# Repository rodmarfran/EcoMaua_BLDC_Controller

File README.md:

# EcoMaua_Dev
Repositório para desenvolvimentos do EcoMaua

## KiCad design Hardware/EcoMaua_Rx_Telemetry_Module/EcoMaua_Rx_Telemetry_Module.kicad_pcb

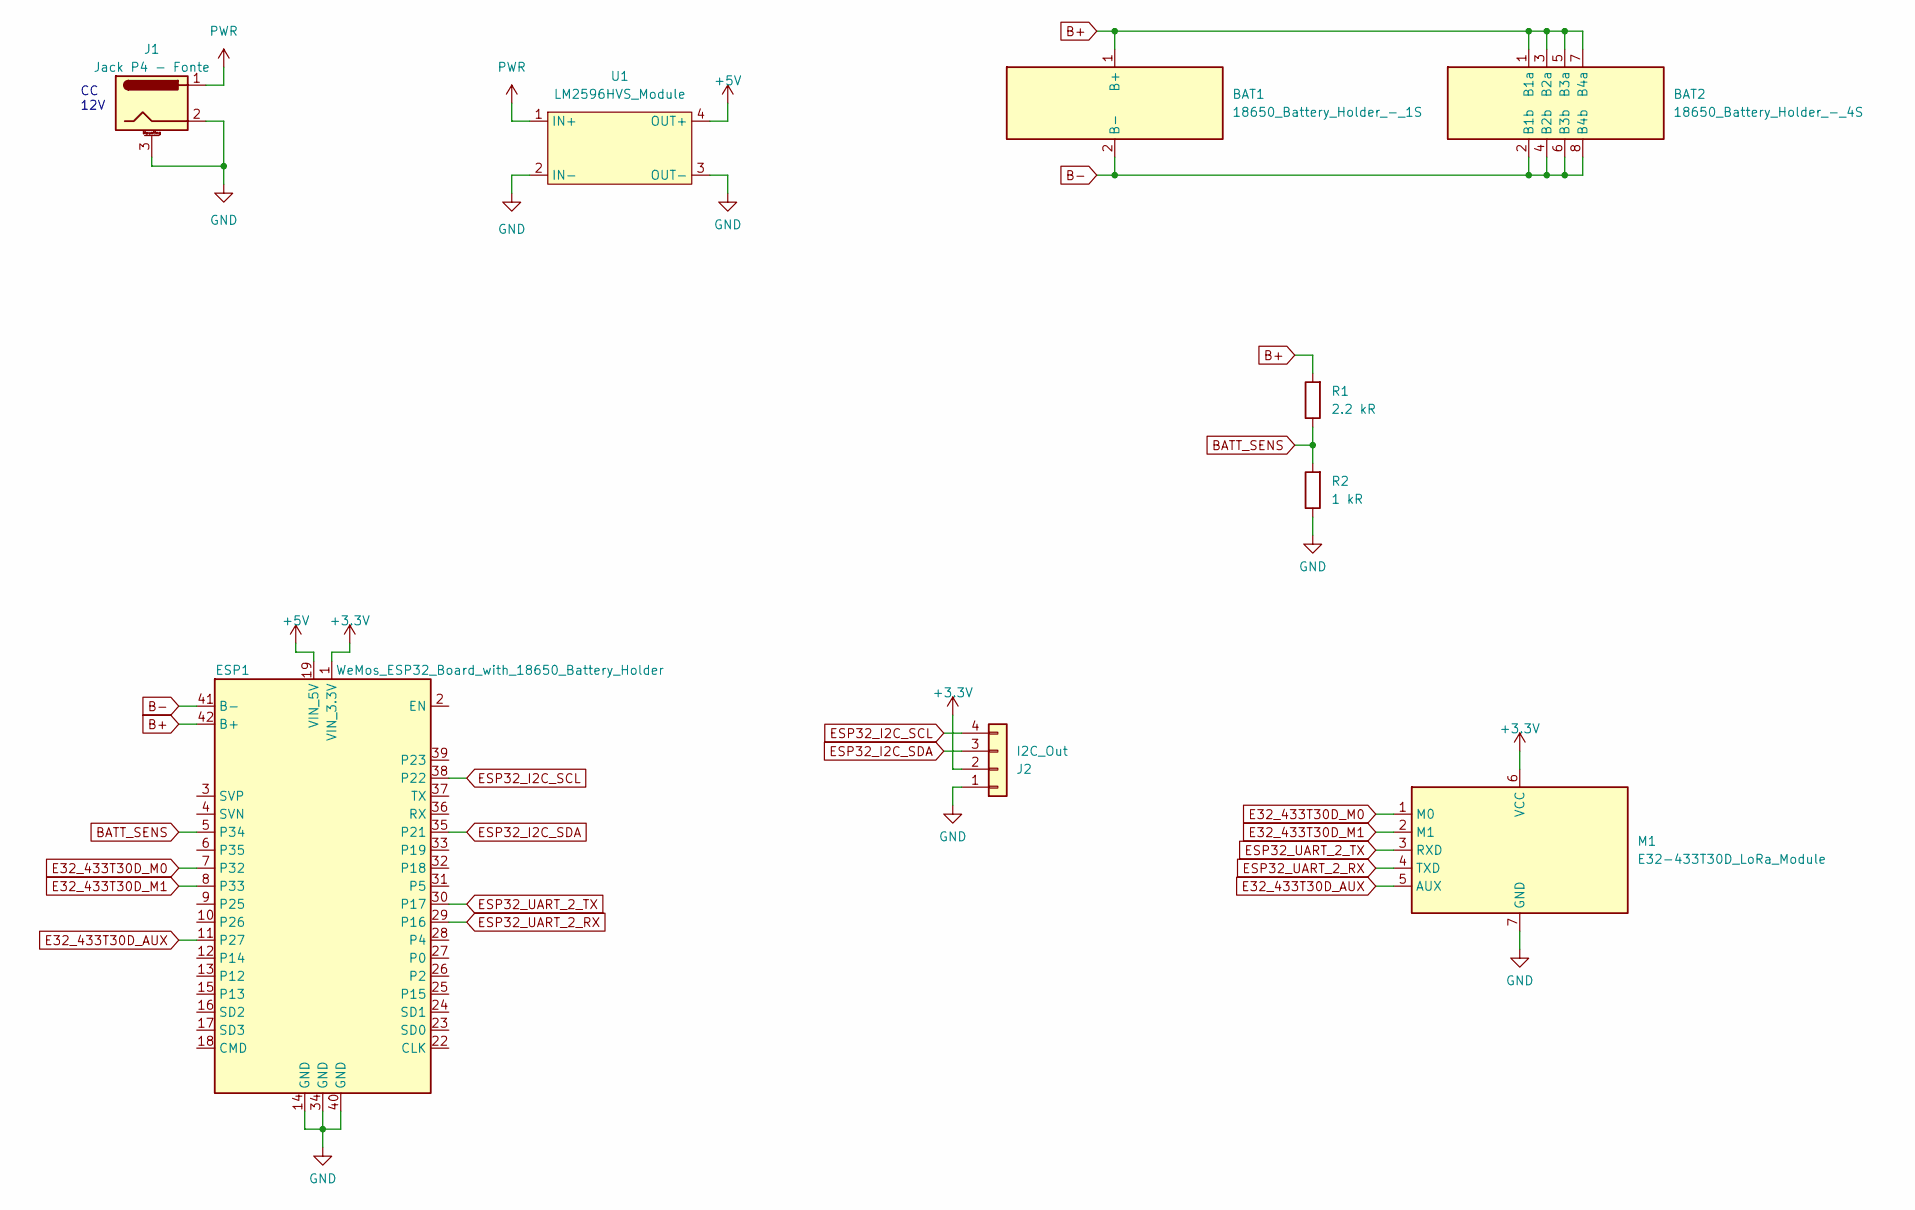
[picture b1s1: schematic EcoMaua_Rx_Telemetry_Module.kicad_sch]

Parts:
BAT1: 18650_Battery_Holder_-_1S; 18650 Battery Holder - 1S
BAT2: 18650_Battery_Holder_-_4S; 18650 Battery Holder - 4S
ESP1: WeMos_ESP32_Board_with_18650_Battery_Holder; WeMos ESP32 Board with 18650 Battery Holder
J1: Jack P4 - Fonte; BarrelJack_Horizontal
J2: I2C_Out; PinHeader_1x04_P2.54mm_Vertical
M1: E32-433T30D_LoRa_Module; E32-433T30D LoRa Module
R1: 2.2 kR; R_Axial_DIN0207_L6.3mm_D2.5mm_P10.16mm_Horizontal
R2: 1 kR; R_Axial_DIN0207_L6.3mm_D2.5mm_P10.16mm_Horizontal
U1: LM2596HVS_Module; LM2596HVS_Module_PDIP

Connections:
+3.3V: ESP1.1 (VIN_3.3V), J2.2, M1.6 (VCC)
+5V: ESP1.19 (VIN_5V), U1.4 (OUT+)
B+: BAT1.1 (B+), BAT2.1 (B1a), BAT2.3 (B2a), BAT2.5 (B3a), BAT2.7 (B4a), ESP1.42 (B+), R1.2
B-: BAT1.2 (B-), BAT2.2 (B1b), BAT2.4 (B2b), BAT2.6 (B3b), BAT2.8 (B4b), ESP1.41 (B-)
BATT_SENS: ESP1.5 (P34), R1.1, R2.2
E32_433T30D_AUX: ESP1.11 (P27), M1.5 (AUX)
E32_433T30D_M0: ESP1.7 (P32), M1.1 (M0)
E32_433T30D_M1: ESP1.8 (P33), M1.2 (M1)
ESP32_I2C_SCL: ESP1.38 (P22), J2.4
ESP32_I2C_SDA: ESP1.35 (P21), J2.3
ESP32_UART_2_RX: ESP1.29 (P16), M1.4 (TXD)
ESP32_UART_2_TX: ESP1.30 (P17), M1.3 (RXD)
GND: ESP1.14 (GND), ESP1.34 (GND), ESP1.40 (GND), J1.2, J1.3 (MountPin), J2.1, M1.7 (GND), R2.1, U1.2 (IN-), U1.3 (OUT-)
PWR: J1.1, U1.1 (IN+)

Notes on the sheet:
CC 12V

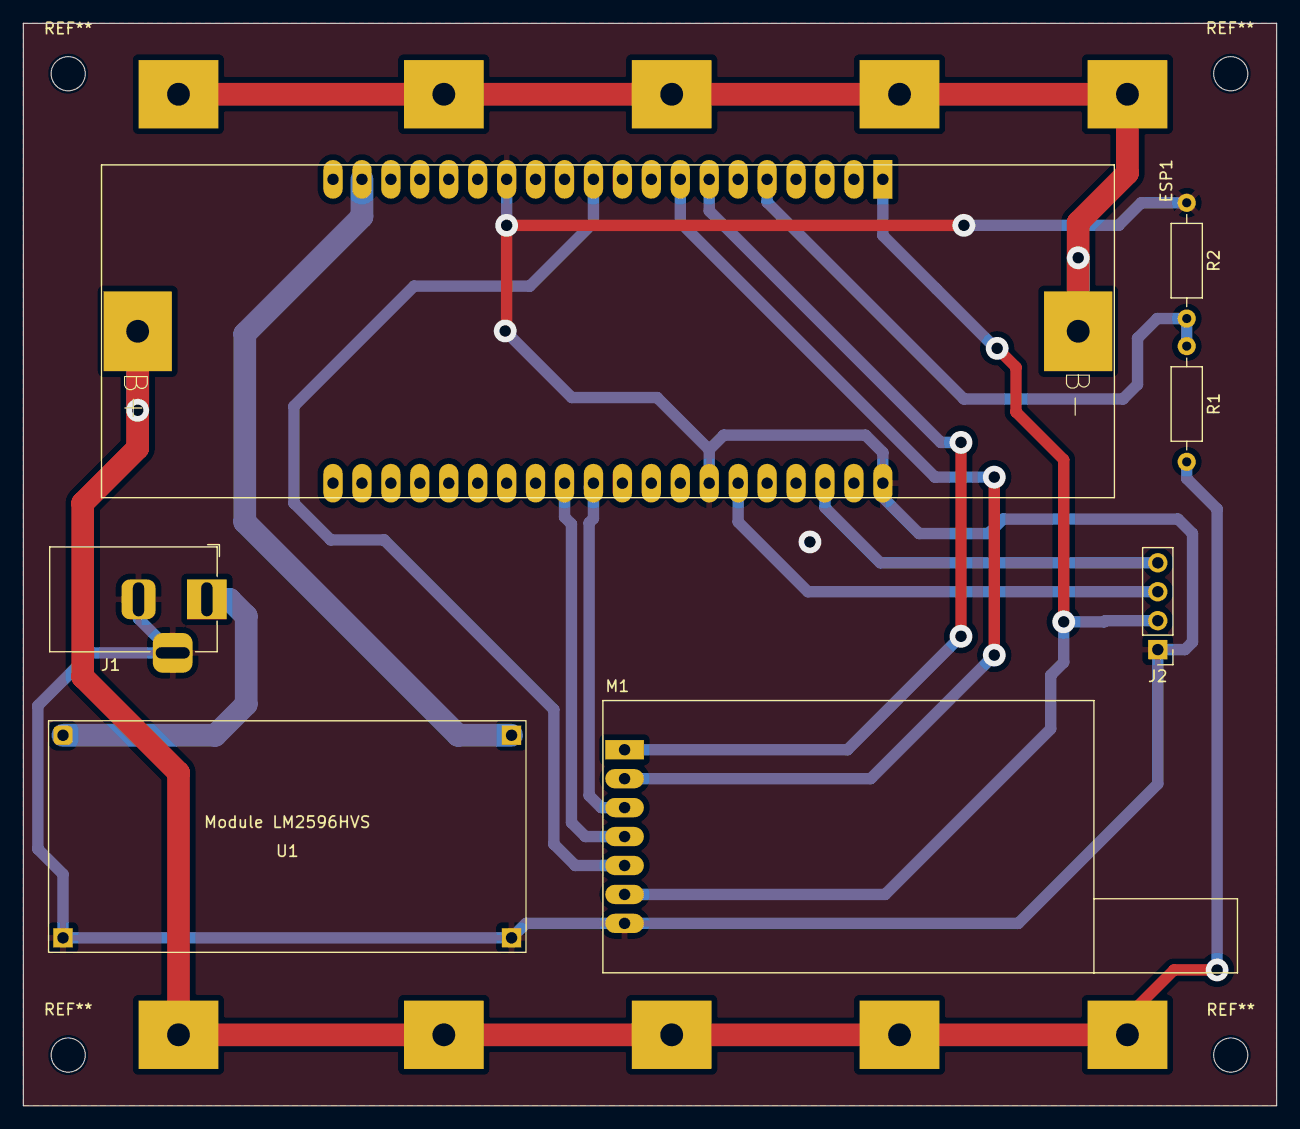
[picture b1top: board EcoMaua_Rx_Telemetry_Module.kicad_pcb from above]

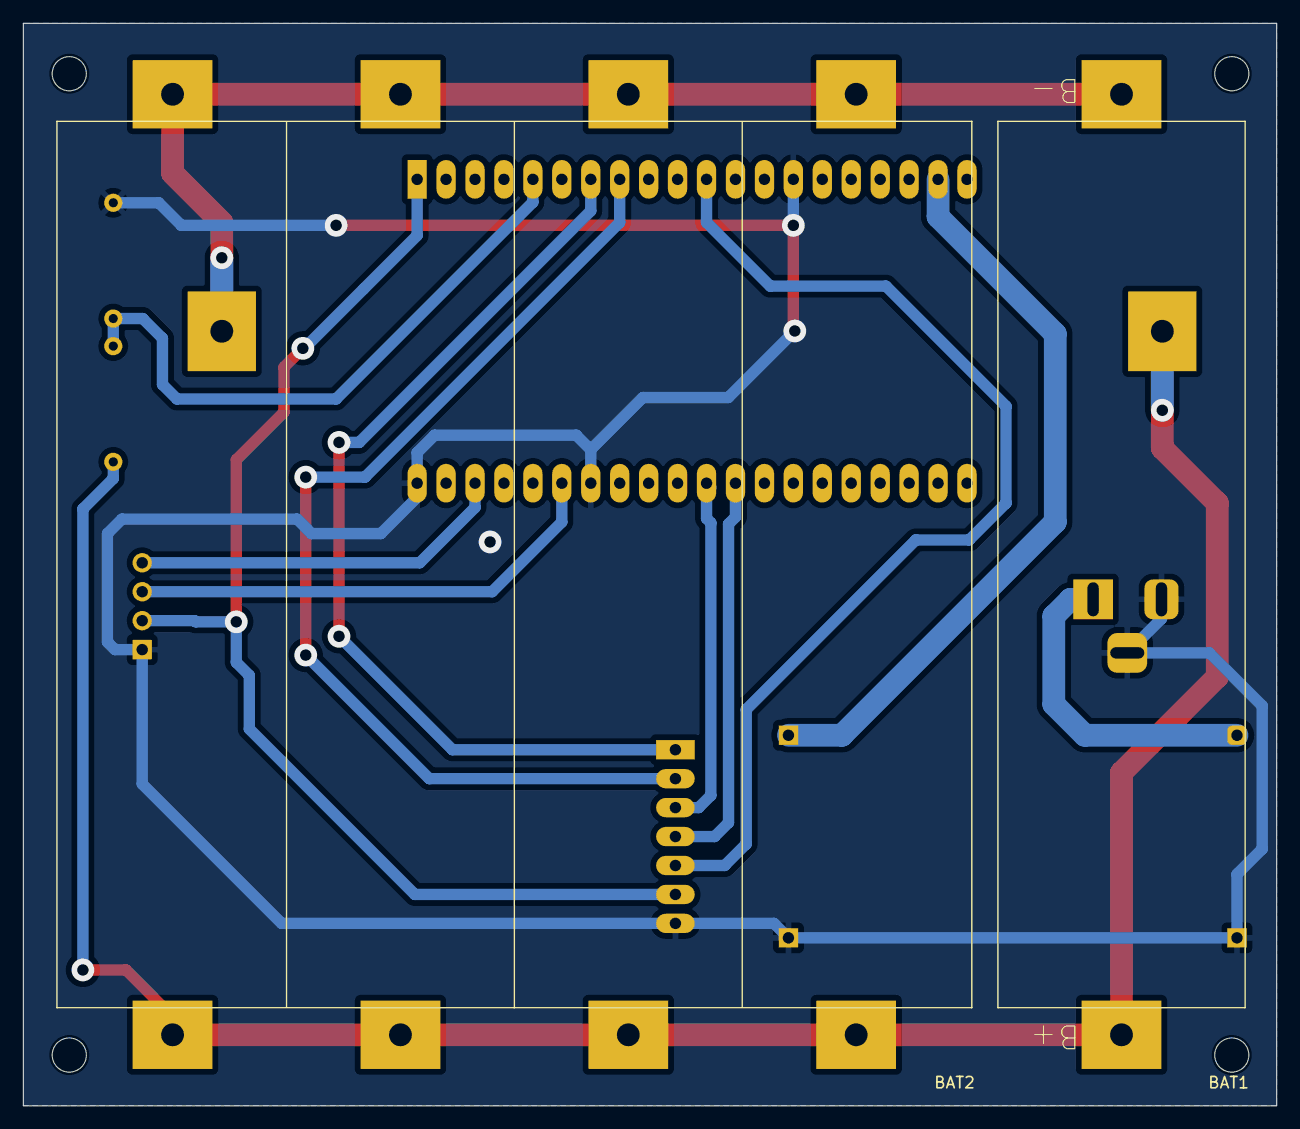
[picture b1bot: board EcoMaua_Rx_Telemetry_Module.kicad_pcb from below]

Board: 2 copper layers, 110.0 x 95.0 mm, 9 parts (2 on the bottom side), 14 nets.

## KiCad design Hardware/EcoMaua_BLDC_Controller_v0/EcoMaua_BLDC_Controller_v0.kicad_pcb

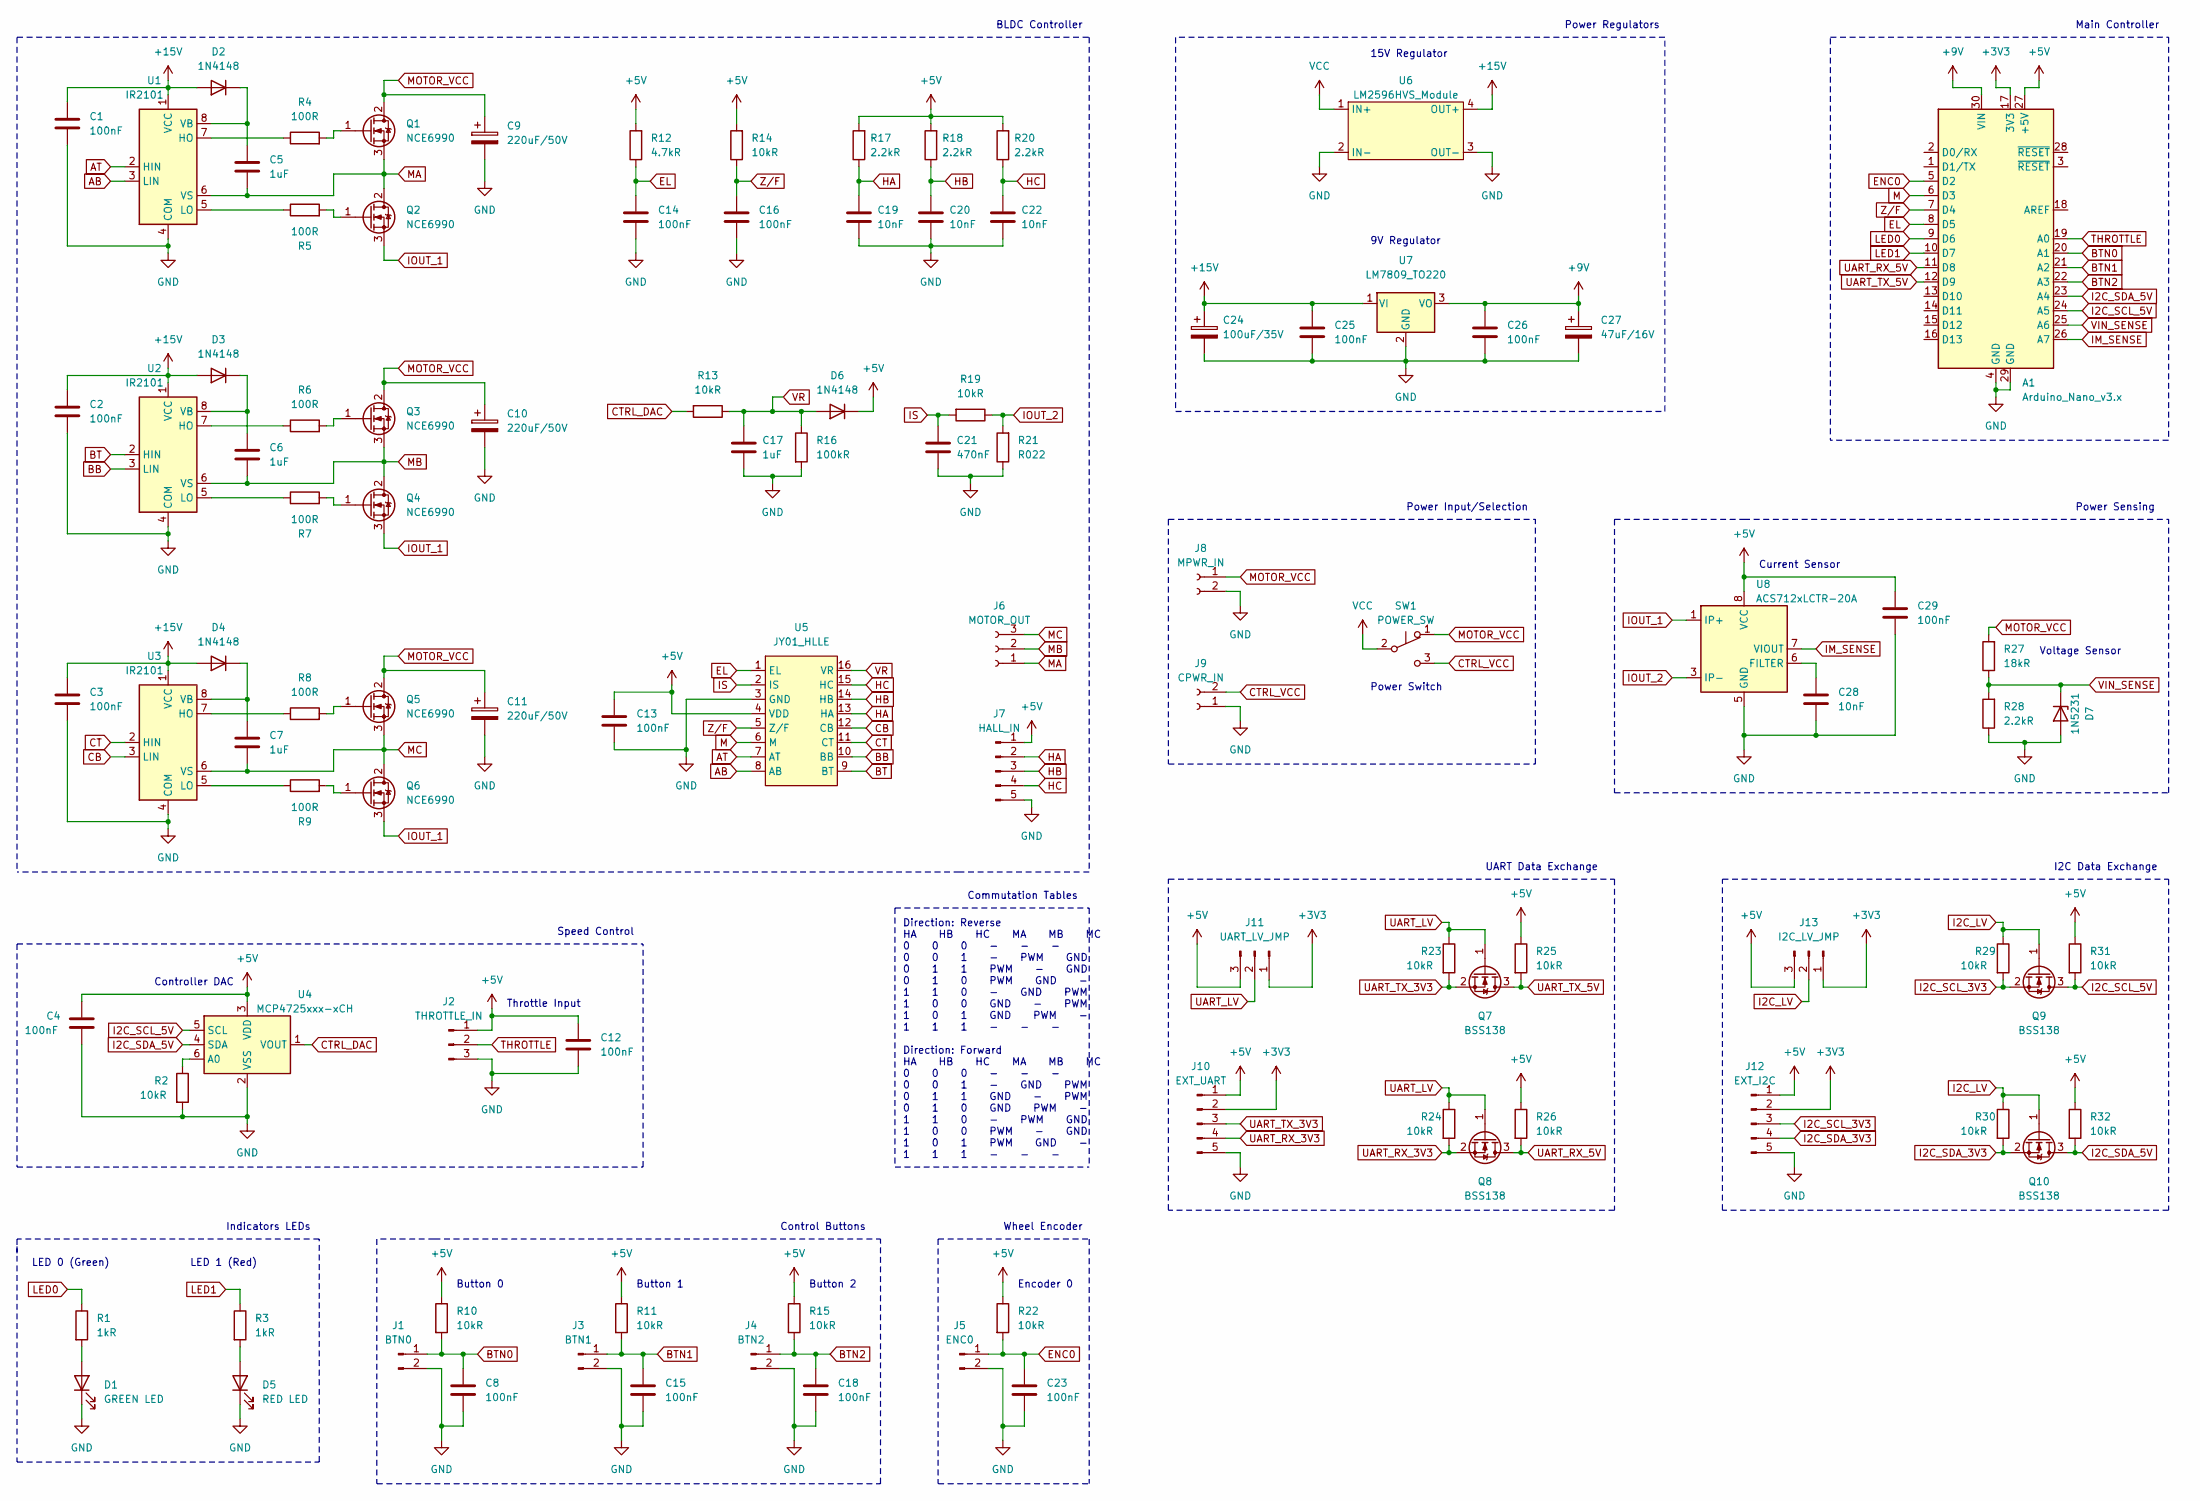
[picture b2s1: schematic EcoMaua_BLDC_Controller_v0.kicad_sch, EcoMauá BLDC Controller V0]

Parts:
A1: Arduino_Nano_v3.x; Arduino_Nano
C1, C2, C3, C4, C8, C12, C13, C14, C15, C16, C18, C23, C25, C26, C29: 100nF; C_0805_2012Metric
C5, C6, C7, C17: 1uF; C_0805_2012Metric
C9, C10, C11: 220uF/50V; CP_Elec_10x10.5
C19, C20, C22, C28: 10nF; C_0805_2012Metric
C21: 470nF; C_0805_2012Metric
C24: 100uF/35V; CP_Elec_6.3x7.7
C27: 47uF/16V; CP_Elec_5x5.4
D1: GREEN LED; LED_0805_2012Metric
D2, D3, D4, D6: 1N4148; D_MiniMELF
D5: RED LED; LED_0805_2012Metric
D7: 1N5231; D_MiniMELF
J1: BTN0; PinHeader_1x02_P2.54mm_Vertical
J2: THROTTLE_IN; PinHeader_1x03_P2.54mm_Vertical
J3: BTN1; PinHeader_1x02_P2.54mm_Vertical
J4: BTN2; PinHeader_1x02_P2.54mm_Vertical
J5: ENC0; PinHeader_1x02_P2.54mm_Vertical
J6: MOTOR_OUT; PhoenixContact_MSTBVA_2,5_3-G-5,08_1x03_P5.08mm_Vertical
J7: HALL_IN; PinHeader_1x05_P2.54mm_Vertical
J8: MPWR_IN; PhoenixContact_MSTBVA_2,5_2-G-5,08_1x02_P5.08mm_Vertical
J9: CPWR_IN; PinHeader_1x02_P2.54mm_Vertical
J10: EXT_UART; PinHeader_1x05_P2.54mm_Vertical
J11: UART_LV_JMP; PinHeader_1x03_P2.54mm_Vertical
J12: EXT_I2C; PinHeader_1x05_P2.54mm_Vertical
J13: I2C_LV_JMP; PinHeader_1x03_P2.54mm_Vertical
Q1, Q2, Q3, Q4, Q5, Q6: NCE6990; TO-220-3_Horizontal_TabUp_NoHole_F
Q7, Q8, Q9, Q10: BSS138; SOT-23
R1, R3: 1kR; R_0805_2012Metric
R2, R10, R11, R13, R14, R15, R19, R22, R23, R24, R25, R26, R29, R30, R31, R32: 10kR; R_0805_2012Metric
R4, R5, R6, R7, R8, R9: 100R; R_1206_3216Metric
R12: 4.7kR; R_0805_2012Metric
R16: 100kR; R_0805_2012Metric
R17, R18, R20, R28: 2.2kR; R_0805_2012Metric
R21: R022; R_Bare_Metal_Element_L11.4mm_W3.8mm_P10.2mm
R27: 18kR; R_0805_2012Metric
SW1: POWER_SW; SS_Slide_1P2T_SS12F64
U1, U2, U3: IR2101; SOIC-8_3.9x4.9mm_P1.27mm
U4: MCP4725xxx-xCH; SOT-23-6
U5: JY01_HLLE; SOP-16_3.9x9.9mm_P1.27mm
U6: LM2596HVS_Module; LM2596HVS_Module_PDIP
U7: LM7809_TO220; TO-220-3_Horizontal_TabDown
U8: ACS712xLCTR-20A; SOIC-8_3.9x4.9mm_P1.27mm

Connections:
+3V3: A1.17 (3V3), J10.2, J11.1, J12.2, J13.1
+5V: A1.27 (+5V), C4.1, C12.1, C13.1, C29.1, D6.1 (K), J2.1, J7.1, J10.1, J11.3, J12.1, J13.3, R10.1, R11.1, R12.2, R14.2, R15.1, R17.2, R18.2, R20.2, R22.1, R25.1, R26.1, R31.1, R32.1, U4.3 (VDD), U5.4 (VDD), U8.8 (VCC)
+9V: A1.30 (VIN), C26.1, C27.1, U7.3 (VO)
+15V: C1.1, C2.1, C3.1, C24.1, C25.1, D2.2 (A), D3.2 (A), D4.2 (A), U1.1 (VCC), U2.1 (VCC), U3.1 (VCC), U6.4 (OUT+), U7.1 (VI)
AB: U1.3 (LIN), U5.8 (AB)
AT: U1.2 (HIN), U5.7 (AT)
BB: U2.3 (LIN), U5.10 (BB)
BT: U2.2 (HIN), U5.9 (BT)
BTN0: A1.20 (A1), C8.1, J1.1, R10.2
BTN1: A1.21 (A2), C15.1, J3.1, R11.2
BTN2: A1.22 (A3), C18.1, J4.1, R15.2
CB: U3.3 (LIN), U5.12 (CB)
CT: U3.2 (HIN), U5.11 (CT)
CTRL_DAC: R13.2, U4.1 (VOUT)
CTRL_VCC: J9.2, SW1.3 (C)
EL: A1.8 (D5), C14.1, R12.1, U5.1 (EL)
ENC0: A1.5 (D2), C23.1, J5.1, R22.2
GND: A1.4 (GND), A1.29 (GND), C1.2, C2.2, C3.2, C4.2, C8.2, C9.2, C10.2, C11.2, C12.2, C13.2, C14.2, C15.2, C16.2, C17.2, C18.2, C19.2, C20.2, C21.2, C22.2, C23.2, C24.2, C25.2, C26.2, C27.2, C28.2, C29.2, D1.1 (K), D5.1 (K), D7.2 (A), J1.2, J2.3, J3.2, J4.2, J5.2, J7.5, J8.2, J9.1, J10.5, J12.5, R2.2, R16.2, R21.1, R28.1, U1.4 (COM), U2.4 (COM), U3.4 (COM), U4.2 (VSS), U5.3 (GND), U6.2 (IN-), U6.3 (OUT-), U7.2 (GND), U8.5 (GND)
HA: C19.1, J7.2, R17.1, U5.13 (HA)
HB: C20.1, J7.3, R18.1, U5.14 (HB)
HC: C22.1, J7.4, R20.1, U5.15 (HC)
I2C_LV: J13.2, Q9.1 (G), Q10.1 (G), R29.1, R30.1
I2C_SCL_3V3: J12.3, Q9.2 (S), R29.2
I2C_SCL_5V: A1.24 (A5), Q9.3 (D), R31.2, U4.5 (SCL)
I2C_SDA_3V3: J12.4, Q10.2 (S), R30.2
I2C_SDA_5V: A1.23 (A4), Q10.3 (D), R32.2, U4.4 (SDA)
IM_SENSE: A1.26 (A7), U8.7 (VIOUT)
IOUT_1: Q2.3 (S), Q4.3 (S), Q6.3 (S), U8.1 (IP+), U8.2 (IP+)
IOUT_2: R19.1, R21.2, U8.3 (IP-), U8.4 (IP-)
IS: C21.1, R19.2, U5.2 (IS)
LED0: A1.9 (D6), R1.1
LED1: A1.10 (D7), R3.1
M: A1.6 (D3), U5.6 (M)
MA: C5.2, J6.1, Q1.3 (S), Q2.2 (D), U1.6 (VS)
MB: C6.2, J6.2, Q3.3 (S), Q4.2 (D), U2.6 (VS)
MC: C7.2, J6.3, Q5.3 (S), Q6.2 (D), U3.6 (VS)
MOTOR_VCC: C9.1, C10.1, C11.1, J8.1, Q1.2 (D), Q3.2 (D), Q5.2 (D), R27.2, SW1.1 (A)
unnamed: C5.1, D2.1 (K), U1.8 (VB)
unnamed: C6.1, D3.1 (K), U2.8 (VB)
unnamed: C7.1, D4.1 (K), U3.8 (VB)
unnamed: C28.1, U8.6 (FILTER)
unnamed: D1.2 (A), R1.2
unnamed: D5.2 (A), R3.2
unnamed: Q1.1 (G), R4.2
unnamed: Q2.1 (G), R5.2
unnamed: Q3.1 (G), R6.2
unnamed: Q4.1 (G), R7.2
unnamed: Q5.1 (G), R8.2
unnamed: Q6.1 (G), R9.2
unnamed: R2.1, U4.6 (A0)
unnamed: R4.1, U1.7 (HO)
unnamed: R5.1, U1.5 (LO)
unnamed: R6.1, U2.7 (HO)
unnamed: R7.1, U2.5 (LO)
unnamed: R8.1, U3.7 (HO)
unnamed: R9.1, U3.5 (LO)
THROTTLE: A1.19 (A0), J2.2
UART_LV: J11.2, Q7.1 (G), Q8.1 (G), R23.1, R24.1
UART_RX_3V3: J10.4, Q8.2 (S), R24.2
UART_RX_5V: A1.11 (D8), Q8.3 (D), R26.2
UART_TX_3V3: J10.3, Q7.2 (S), R23.2
UART_TX_5V: A1.12 (D9), Q7.3 (D), R25.2
VCC: SW1.2 (B), U6.1 (IN+)
VIN_SENSE: A1.25 (A6), D7.1 (K), R27.1, R28.2
VR: C17.1, D6.2 (A), R13.1, R16.1, U5.16 (VR)
Z/F: A1.7 (D4), C16.1, R14.1, U5.5 (Z/F)

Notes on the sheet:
I2C Data Exchange
BLDC Controller
Button 0
Direction: Reverse HA HB HC MA MB MC 0 0 0 - - - 0 0 1 - PWM GND 0 1 1 PWM - GND 0 1 0 PWM GND - 1 1 0 - GND PWM 1 0 0 GND - PWM 1 0 1 GND PWM - 1 1 1 - - - Direction: Forward HA HB HC MA MB MC 0 0 0 - - - 0 0 1 - GND PWM 0 1 1 GND - PWM 0 1 0 GND PWM - 1 1 0 - PWM GND 1 0 0 PWM - GND 1 0 1 PWM GND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
Throttle Input
Commutation Tables
Power Input/Selection
UART Data Exchange
9V Regulator
Wheel Encoder
Button 1
Power Regulators
LED 1 (Red)
Speed Control
Indicators LEDs
Controller DAC
Control Buttons
LED 0 (Green)
Main Controller
Voltage Sensor
Button 2
15V Regulator
Encoder 0
Power Sensing
Current Sensor
Power Switch

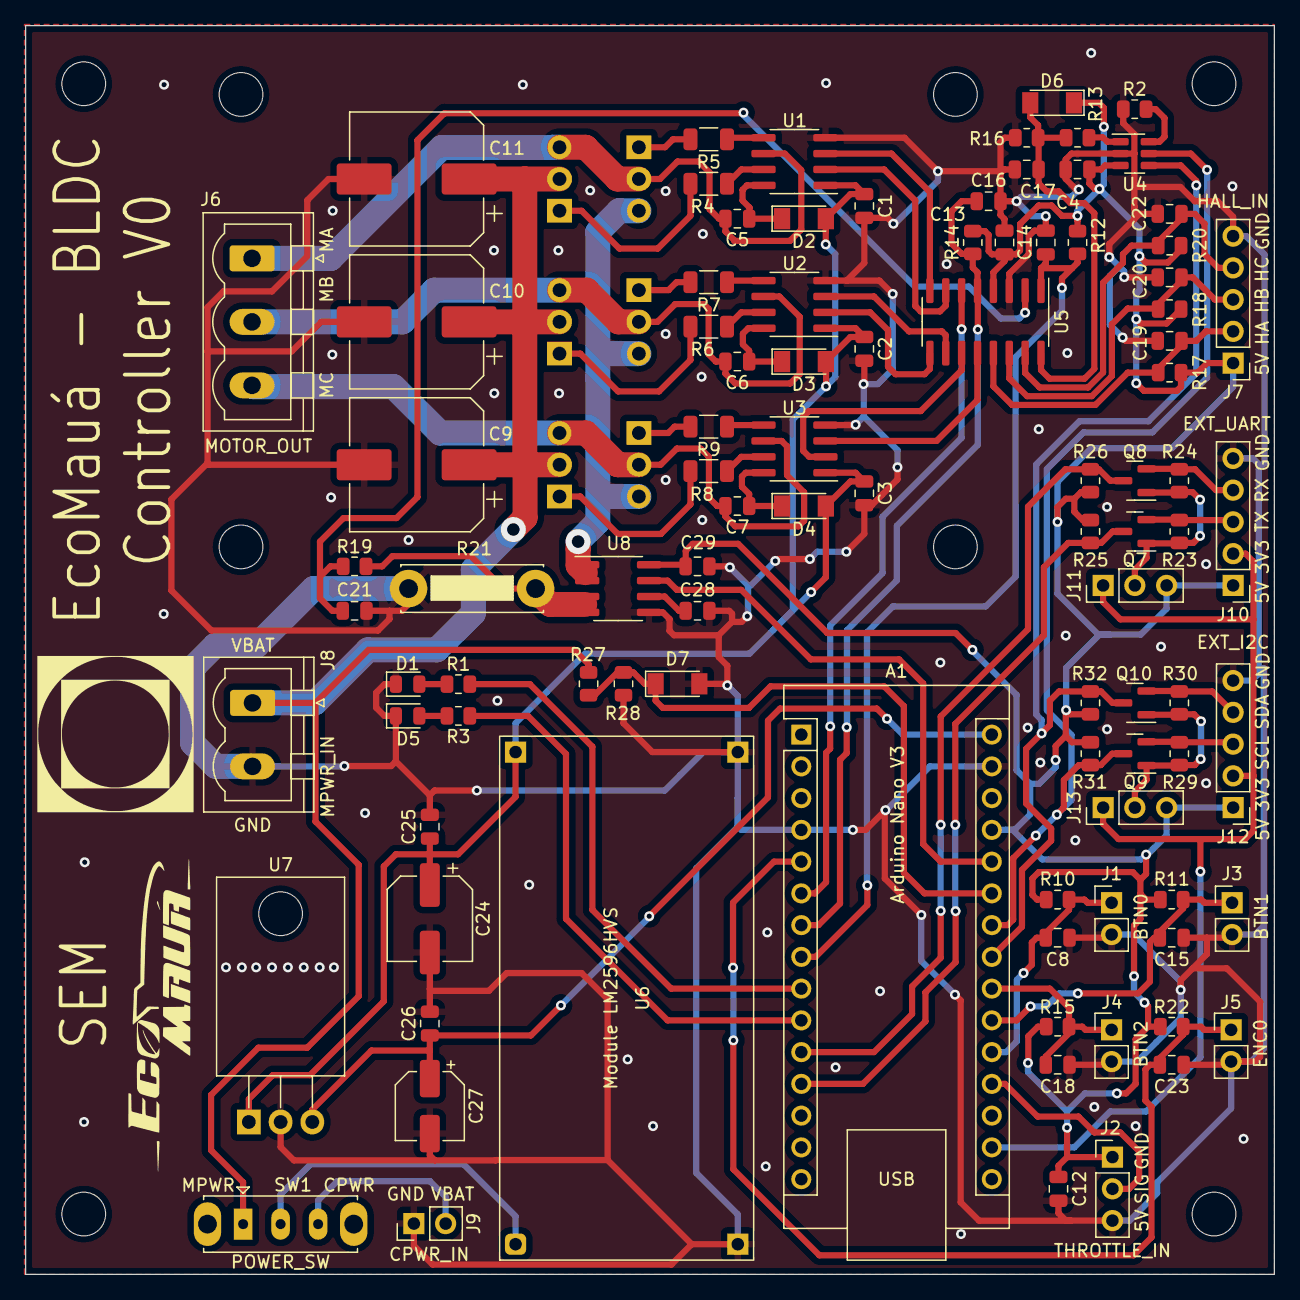
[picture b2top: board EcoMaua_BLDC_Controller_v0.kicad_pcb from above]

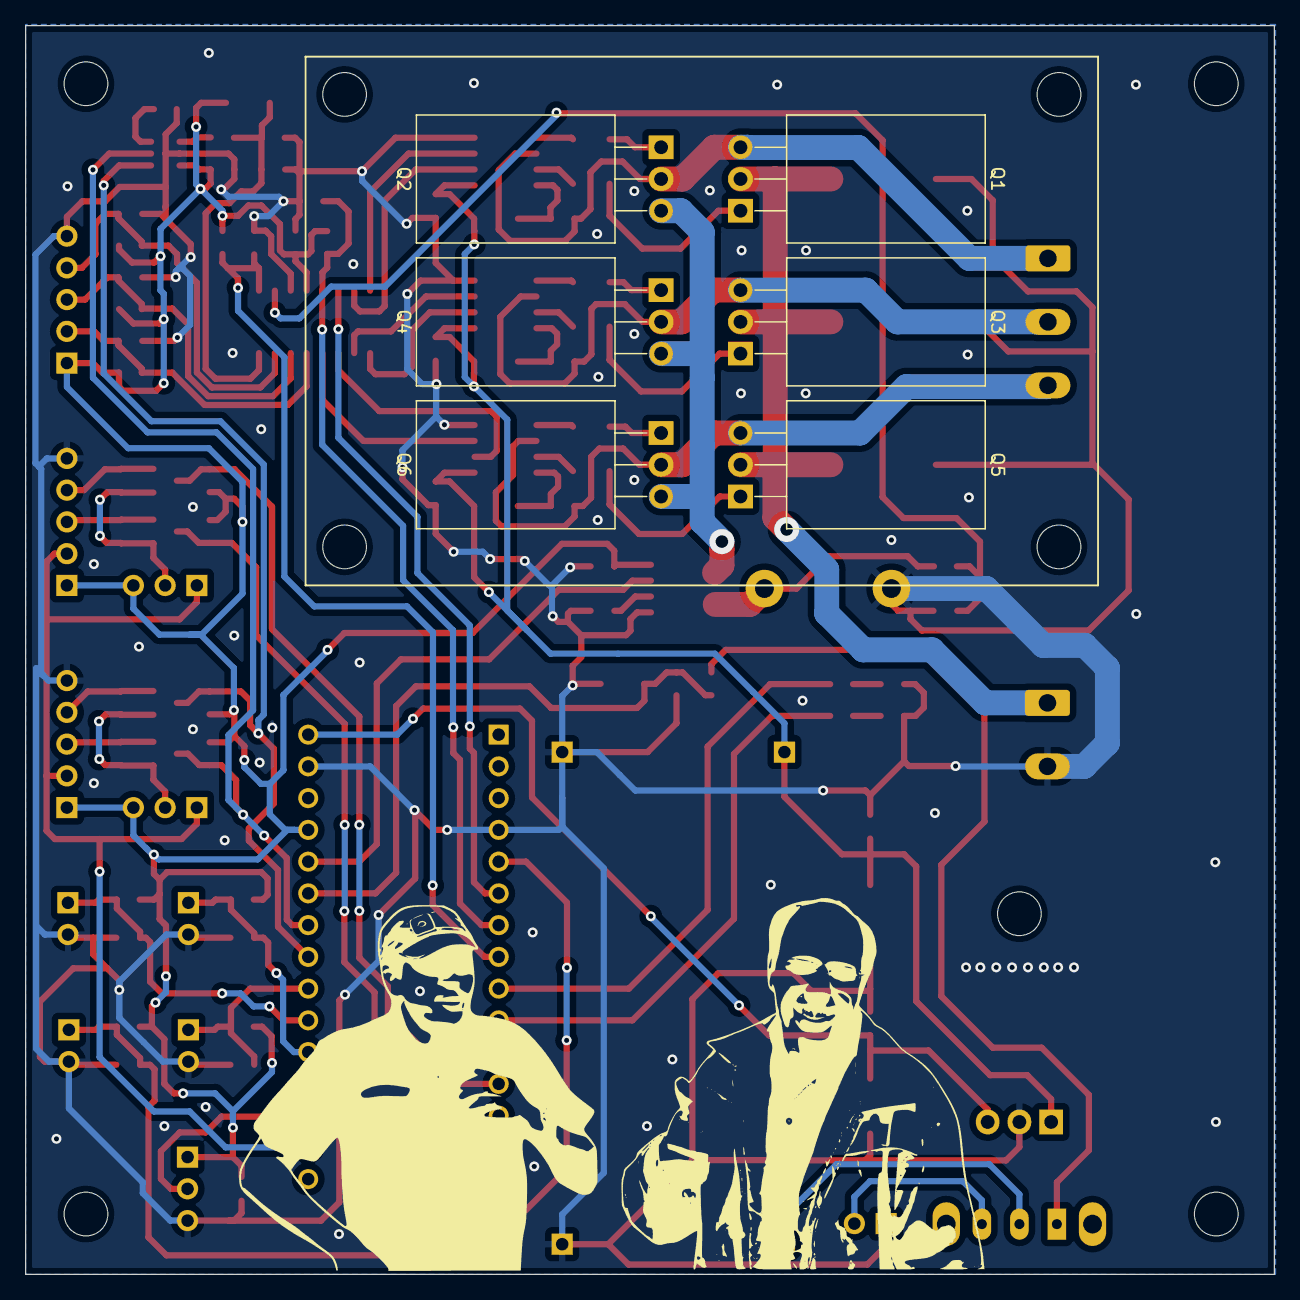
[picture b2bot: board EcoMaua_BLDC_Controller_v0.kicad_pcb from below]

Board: 2 copper layers, 99.9 x 99.9 mm, 109 parts (6 on the bottom side), 66 nets.

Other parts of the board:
MT1, MT2, MT3, MT4, MT5, MT6, MT7, MT8: MountingHole_3.5mm

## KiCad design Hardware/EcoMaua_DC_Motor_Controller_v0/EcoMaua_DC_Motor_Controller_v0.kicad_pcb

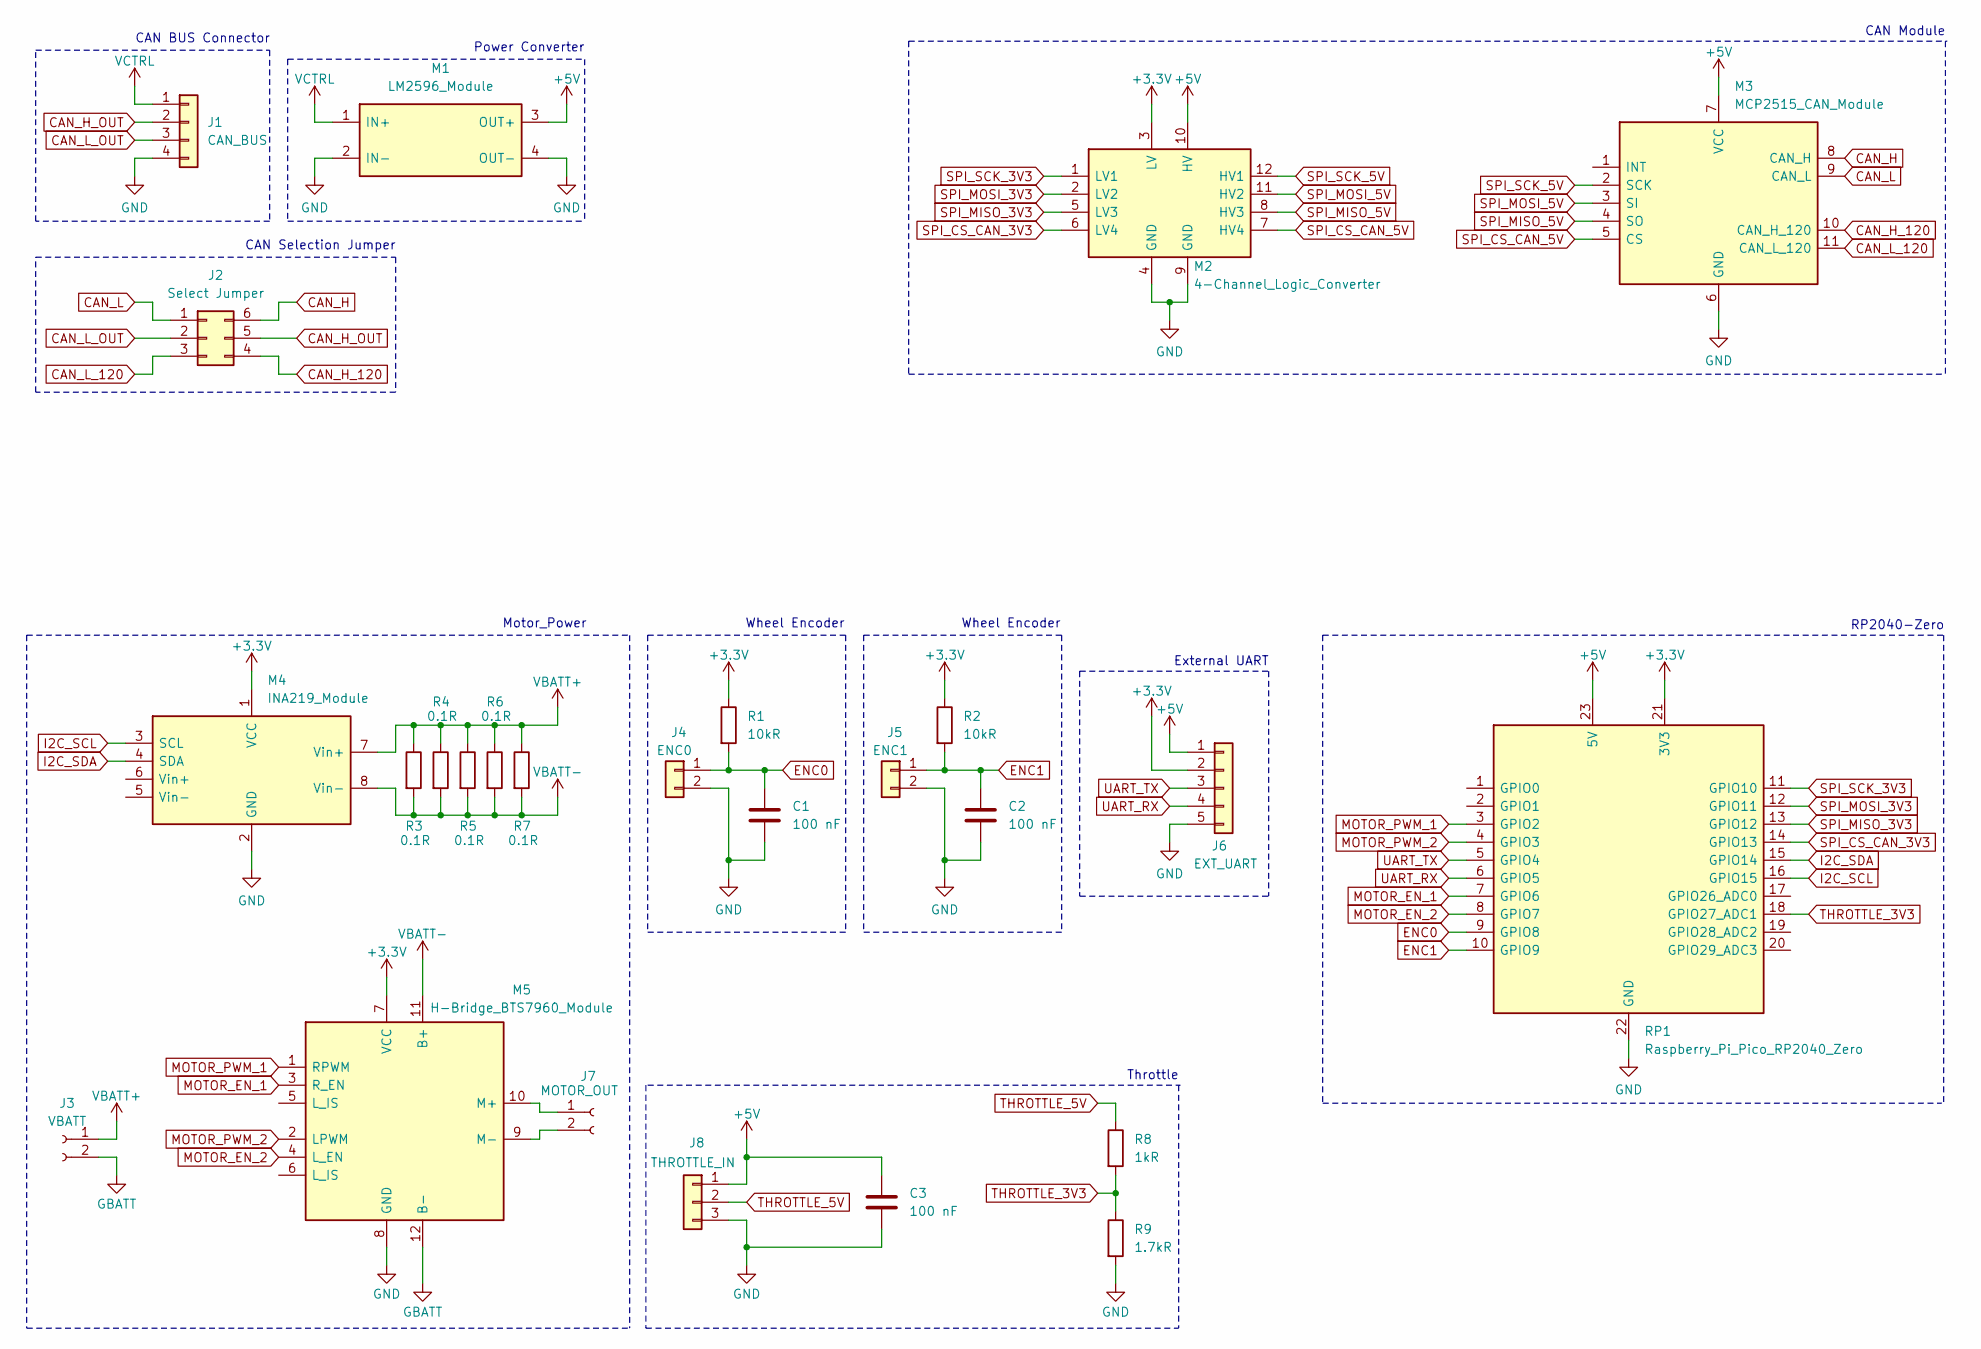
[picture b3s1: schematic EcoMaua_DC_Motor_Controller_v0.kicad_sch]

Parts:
C1, C2, C3: 100 nF; C_Disc_D3.0mm_W1.6mm_P2.50mm
J1: CAN_BUS; PinHeader_1x04_P2.54mm_Vertical_OP
J2: Select Jumper; PinHeader_2x03_P2.54mm_Vertical_OP
J3: VBATT; PhoenixContact_MSTBVA_2,5_2-G-5,08_1x02_P5.08mm_Vertical
J4: ENC0; PinHeader_1x02_P2.54mm_Vertical_OP
J5: ENC1; PinHeader_1x02_P2.54mm_Vertical_OP
J6: EXT_UART; PinHeader_1x05_P2.54mm_Vertical_OP
J7: MOTOR_OUT; PhoenixContact_MSTBVA_2,5_2-G-5,08_1x02_P5.08mm_Vertical
J8: THROTTLE_IN; PinHeader_1x03_P2.54mm_Vertical_OP
M1: LM2596_Module; LM2596 Module
M2: 4-Channel_Logic_Converter; 4-Channel Logic Converter
M3: MCP2515_CAN_Module; MCP2515_CAN Module
M4: INA219_Module; INA219 Module
M5: H-Bridge_BTS7960_Module; H-Bridge BTS7960 Module
R1, R2: 10kR; R_Axial_DIN0207_L6.3mm_D2.5mm_P15.24mm_Horizontal
R3, R4, R5, R6, R7: 0.1R; R_Axial_DIN0309_L9.0mm_D3.2mm_P25.40mm_Horizontal
R8: 1kR; R_Axial_DIN0207_L6.3mm_D2.5mm_P15.24mm_Horizontal
R9: 1.7kR; R_Axial_DIN0207_L6.3mm_D2.5mm_P15.24mm_Horizontal
RP1: Raspberry_Pi_Pico_RP2040_Zero; Raspberry Pi Pico RP2040 Zero

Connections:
+3.3V: J6.2, M2.3 (LV), M4.1 (VCC), M5.7 (VCC), R1.1, R2.1, RP1.21 (3V3)
+5V: C3.1, J6.1, J8.1, M1.3 (OUT+), M2.10 (HV), M3.7 (VCC), RP1.23 (5V)
CAN_H: J2.6, M3.8 (CAN_H)
CAN_H_120: J2.4, M3.10 (CAN_H_120)
CAN_H_OUT: J1.2, J2.5
CAN_L: J2.1, M3.9 (CAN_L)
CAN_L_120: J2.3, M3.11 (CAN_L_120)
CAN_L_OUT: J1.3, J2.2
ENC0: C1.1, J4.1, R1.2, RP1.9 (GPIO8)
ENC1: C2.1, J5.1, R2.2, RP1.10 (GPIO9)
GBATT: J3.2, M5.12 (B-)
GND: C1.2, C2.2, C3.2, J1.4, J4.2, J5.2, J6.5, J8.3, M1.2 (IN-), M1.4 (OUT-), M2.4 (GND), M2.9 (GND), M3.6 (GND), M4.2 (GND), M5.8 (GND), R9.2, RP1.22 (GND)
I2C_SCL: M4.3 (SCL), RP1.16 (GPIO15)
I2C_SDA: M4.4 (SDA), RP1.15 (GPIO14)
MOTOR_EN_1: M5.3 (R_EN), RP1.7 (GPIO6)
MOTOR_EN_2: M5.4 (L_EN), RP1.8 (GPIO7)
MOTOR_PWM_1: M5.1 (RPWM), RP1.3 (GPIO2)
MOTOR_PWM_2: M5.2 (LPWM), RP1.4 (GPIO3)
unnamed: J7.1, M5.10 (M+)
unnamed: J7.2, M5.9 (M-)
SPI_CS_CAN_3V3: M2.6 (LV4), RP1.14 (GPIO13)
SPI_CS_CAN_5V: M2.7 (HV4), M3.5 (CS)
SPI_MISO_3V3: M2.5 (LV3), RP1.13 (GPIO12)
SPI_MISO_5V: M2.8 (HV3), M3.4 (SO)
SPI_MOSI_3V3: M2.2 (LV2), RP1.12 (GPIO11)
SPI_MOSI_5V: M2.11 (HV2), M3.3 (SI)
SPI_SCK_3V3: M2.1 (LV1), RP1.11 (GPIO10)
SPI_SCK_5V: M2.12 (HV1), M3.2 (SCK)
THROTTLE_3V3: R8.2, R9.1, RP1.18 (GPIO27_ADC1)
THROTTLE_5V: J8.2, R8.1
UART_RX: J6.4, RP1.6 (GPIO5)
UART_TX: J6.3, RP1.5 (GPIO4)
VBATT+: J3.1, M4.7 (Vin+), R3.1, R4.1, R5.1, R6.1, R7.1
VBATT-: M4.8 (Vin-), M5.11 (B+), R3.2, R4.2, R5.2, R6.2, R7.2
VCTRL: J1.1, M1.1 (IN+)

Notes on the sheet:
CAN BUS Connector
Wheel Encoder
Throttle
CAN Module
CAN Selection Jumper
External UART
Motor_Power
RP2040-Zero
Power Converter

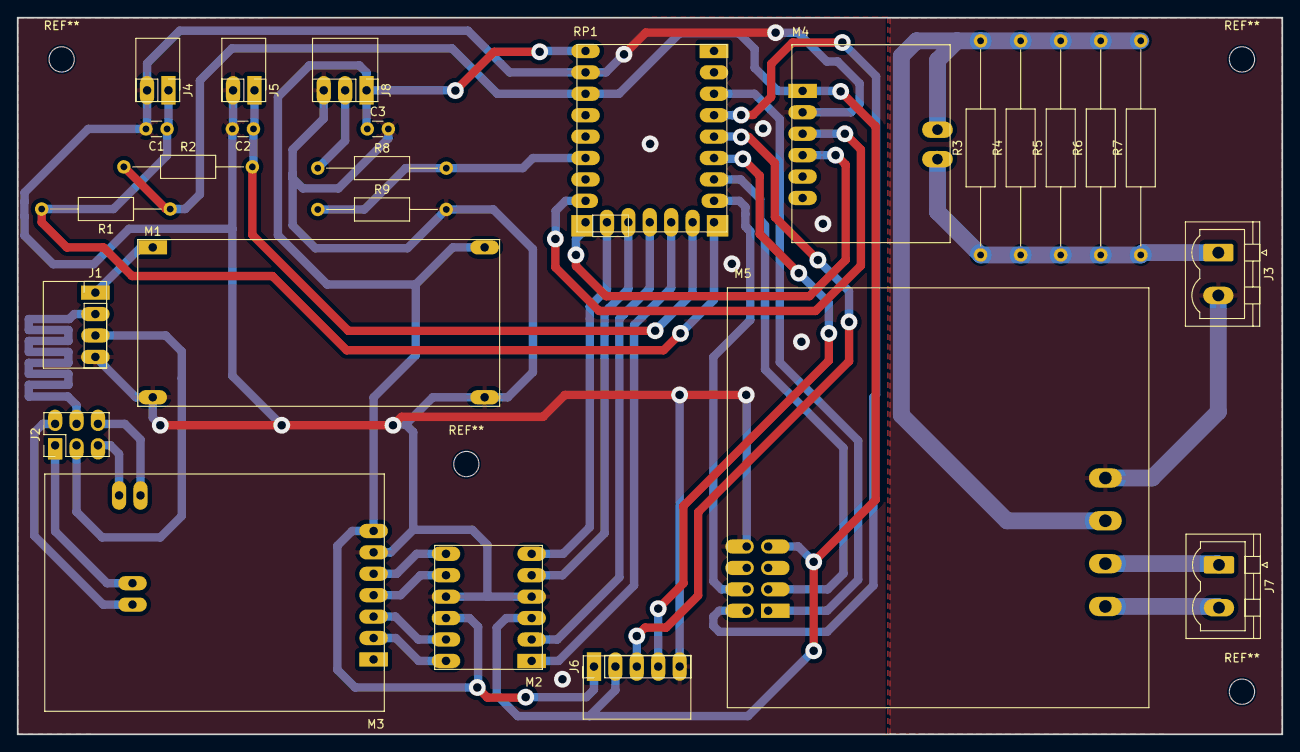
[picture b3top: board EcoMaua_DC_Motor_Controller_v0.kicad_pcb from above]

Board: 2 copper layers, 150.0 x 85.0 mm, 26 parts (0 on the bottom side), 35 nets.
